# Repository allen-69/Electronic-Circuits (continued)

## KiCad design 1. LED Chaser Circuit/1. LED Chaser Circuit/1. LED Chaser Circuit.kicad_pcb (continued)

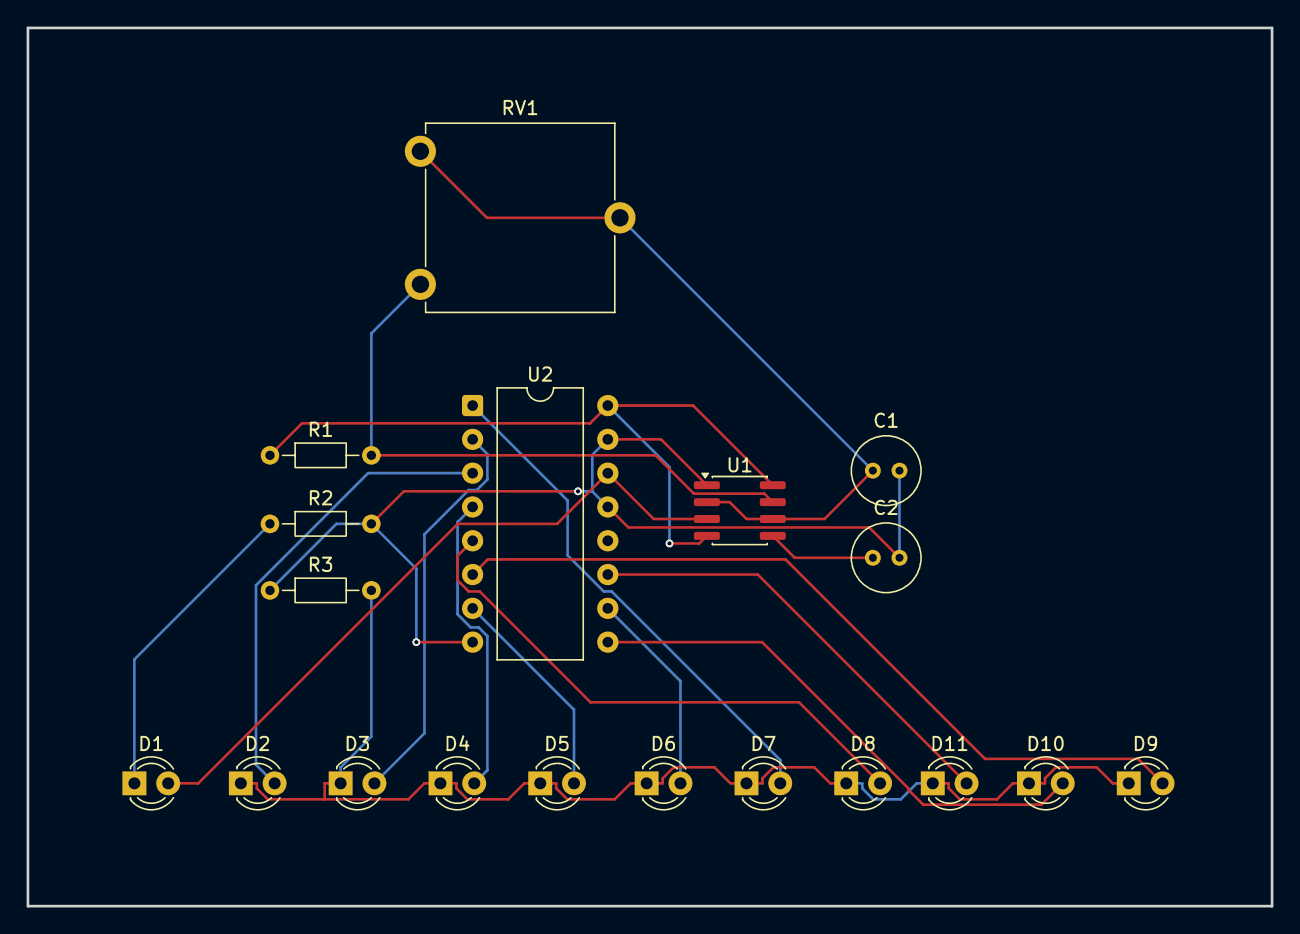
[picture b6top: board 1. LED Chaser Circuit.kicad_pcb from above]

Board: 2 copper layers, 93.5 x 66.0 mm, 19 parts (0 on the bottom side), 18 nets.

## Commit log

2026-06-25 Add files via upload
    Add LED Chaser KiCad project
2026-06-25 Add files via upload
    Add High Power Audio Amplifier KiCad project
2026-06-25 Add files via upload
    Add Inverter UPS Circuit KiCad project
